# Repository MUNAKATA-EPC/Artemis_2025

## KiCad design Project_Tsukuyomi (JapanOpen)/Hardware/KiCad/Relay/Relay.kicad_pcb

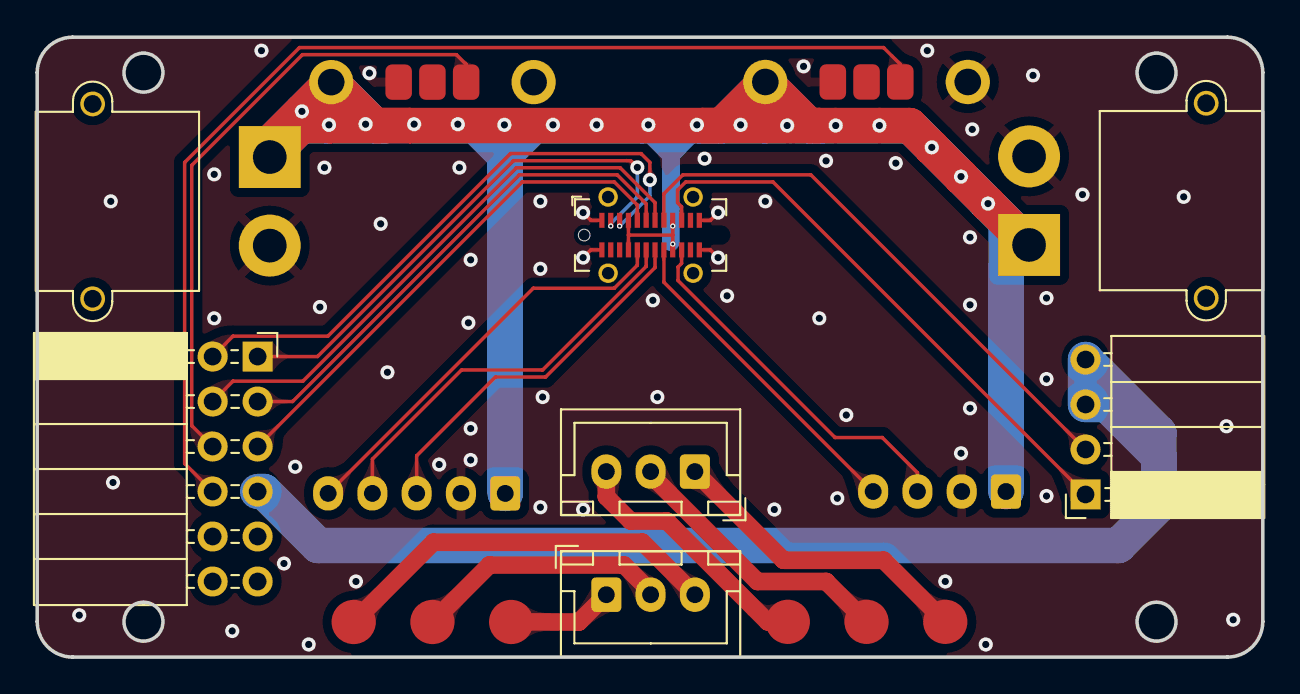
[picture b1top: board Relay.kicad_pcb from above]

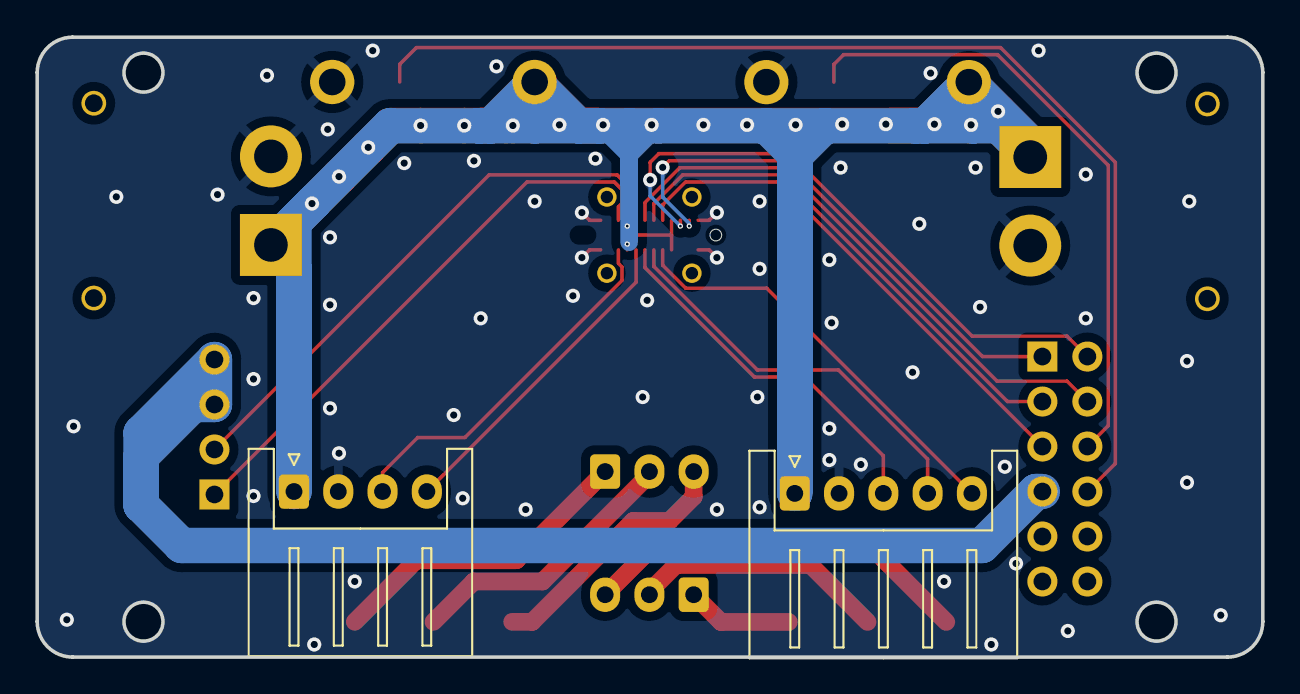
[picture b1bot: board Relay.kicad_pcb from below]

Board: 2 copper layers, 69.2 x 35.0 mm, 11 parts (2 on the bottom side), 23 nets.

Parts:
J1: UJ32-C-V-G-TH-5-P24-TR; USB_C_Receptacle_GCT_USB4115-03-C
J2: Conn_01x05_Socket; JST_XH_S5B-XH-A_1x05_P2.50mm_Horizontal
J3, J4: Conn_01x02_Socket; AMASS_XT30PW-M_1x02_P2.50mm_Horizontal
J5, J6: Conn_01x03_Socket; JST_XH_B3B-XH-A_1x03_P2.50mm_Vertical
J7: Conn_01x04_Socket; PinSocket_1x04_P2.54mm_Horizontal
J8: Conn_01x08_Socket; PinSocket_2x06_P2.54mm_Horizontal
J9: Conn_01x04_Socket; JST_XH_S4B-XH-A_1x04_P2.50mm_Horizontal
U1, U2: ESC_20A

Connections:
+12V: J1.A4 (VBUS), J1.A9 (VBUS), J1.B4 (VBUS), J1.B9 (VBUS), J2.1, J3.1, J4.1, J9.1, U1.1 (VDDM), U2.1 (VDDM)
+48V: J7.3, J7.4, J8.7
/BLDC1: J8.6, U1.3 (PWM)
/BLDC2: J8.8, U2.3 (PWM)
/FET1: J1.A6 (DP1), J8.3
/FET2: J1.A7 (DN1), J8.4
/FET3: J1.A5 (CC1), J8.5
/LineRX: J1.B6 (DP2), J2.3
/LineTX: J1.B7 (DN2), J2.4
/Line_NeoPixel: J1.B8 (SBU2), J2.5
/MDRX: J1.A3 (SSTXN1), J8.2
/MDTX: J1.A2 (SSTXP1), J8.1
/MouseRX: J1.B3 (SSTXN2), J9.3
/MouseTX: J1.B5 (CC2), J9.4
/OUT1A: J5.1, U1.6 (OUT_A)
/OUT1B: J5.2, U1.7 (OUT_B)
/OUT1C: J5.3, U1.8 (OUT_C)
/OUT2A: J6.1, U2.6 (OUT_A)
/OUT2B: J6.2, U2.7 (OUT_B)
/OUT2C: J6.3, U2.8 (OUT_C)
/UART_RX: J1.A8 (SBU1), J7.2
/UART_TX: J1.A10 (SSRXN2), J7.1
GND: J1.A1 (GND), J1.A12 (GND), J1.B1 (GND), J1.B12 (GND), J2.2, J3.2, J4.2, J9.2, U1.2 (GND), U1.5 (GND), U2.2 (GND), U2.5 (GND)

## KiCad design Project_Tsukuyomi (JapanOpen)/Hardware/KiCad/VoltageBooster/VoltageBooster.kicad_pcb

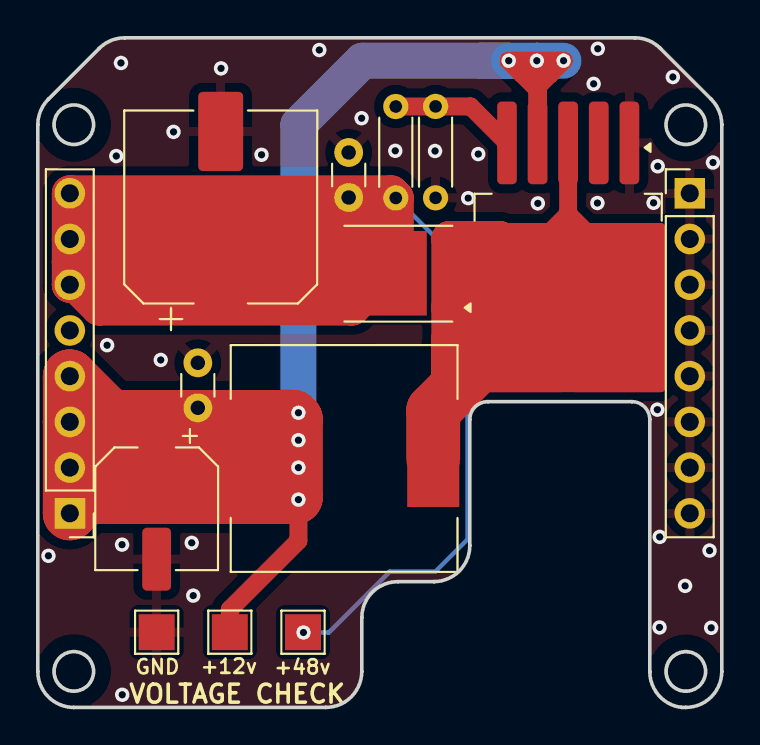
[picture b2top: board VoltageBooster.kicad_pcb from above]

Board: 2 copper layers, 38.0 x 37.2 mm, 11 parts (0 on the bottom side), 5 nets.

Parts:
C1: 47μ; CP_Elec_6.3x5.9
C2, C3: 0.1μ; C_Disc_D3.0mm_W1.6mm_P2.50mm
C4: 220μ; CP_Elec_10x10.5
D1: D; Infineon_PG-TDSON-8_6.15x5.15mm
J1, J2: Conn_01x08_Socket; PinHeader_1x08_P2.54mm_Vertical
L1: 47μH; L_12x12mm_H6mm
R1: 47k; R_Axial_DIN0204_L3.6mm_D1.6mm_P5.08mm_Horizontal
R2: 1k; R_Axial_DIN0204_L3.6mm_D1.6mm_P5.08mm_Horizontal
VR1: XL6009; TO-263-5_TabPin3

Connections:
+12V: C1.1, C2.1, J2.1, J2.2, J2.3, J2.4, L1.1, VR1.4 (VIN)
+48V: C3.1, C4.1, D1.1 (K), J2.6, J2.7, J2.8, R1.1
GND: C1.2, C2.2, C3.2, C4.2, J1.1, J1.2, J1.3, J1.4, J1.5, J1.6, J1.7, J1.8, R2.2, VR1.1 (GND)
unnamed: D1.2 (A), L1.2, VR1.3 (SW)
unnamed: R1.2, R2.1, VR1.5 (FB)
